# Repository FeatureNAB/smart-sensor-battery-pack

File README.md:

# Smart Sensor Battery Pack
This is the experimental battery charging PCB designed for my YouTube video. You can see the full build process, design theory, and assembly in the video below:

### Please note: 
The design files in this repository include 10k pull-up resistors on the I2C lines (R9 on SCL, R10 on SDA), tied to the switched `3V_SW` rail, so boards built from the current files need no software workaround.

If you have an earlier board that was built without these resistors, software correction is possible using the XIAO pull-ups, and closing the FET early in the boot cycle:

```
# Force GPIO18 LOW (Turns P-Channel MOSFET on)
# Set priority such that this runs before i2c initialises
esphome:
  on_boot:
    - priority: 1200
      then:
        - lambda: |-
            gpio_config_t io_conf = {};
            io_conf.pin_bit_mask = (1ULL<<18);
            io_conf.mode = GPIO_MODE_OUTPUT;
            io_conf.pull_up_en = GPIO_PULLUP_DISABLE;
            io_conf.pull_down_en = GPIO_PULLDOWN_DISABLE;
            io_conf.intr_type = GPIO_INTR_DISABLE;
            gpio_config(&io_conf);
            gpio_set_level(GPIO_NUM_18, 0);

# Software accessible pullups
i2c:
  sda_pullup_enabled: true
  scl_pullup_enabled: true

```

## ⚠️ Safety Warning
This board involves **Lithium-Ion battery charging**. 
*   This is an **experimental prototype** from a hobbyist. **I am not a professional engineer**. It has **not** been certified by safety agencies (UL, CE, etc.).
*   Lithium batteries can be dangerous if mishandled (risk of thermal runaway, fire, explosion, and serious injury).
*   **DO NOT leave this device unattended with a battery connected**
*   By using these files, you agree that you are solely responsible for verifying the safety of the circuit.

## License & Liability

### 1. Non-Commercial Use Only
This project is shared under the [Creative Commons Attribution-NonCommercial-ShareAlike 4.0 International](https://creativecommons.org/licenses/by-nc-sa/4.0/) license.
*  **You are free to:** Download, modify, and build this for personal use or learning.
*  **You may NOT:** Sell this board, use it in a product you sell, or use these files for any commercial purpose.
*  If you modify and share this design, you must share it under this same license.

### 2. No Liability (Disclaimer)
These files are provided "As Is" for educational purposes ONLY. I am sharing my personal project notes. **I accept no liability for any damage, injury, or loss** that occurs from the use or assembly of these files. Use them at your own risk.

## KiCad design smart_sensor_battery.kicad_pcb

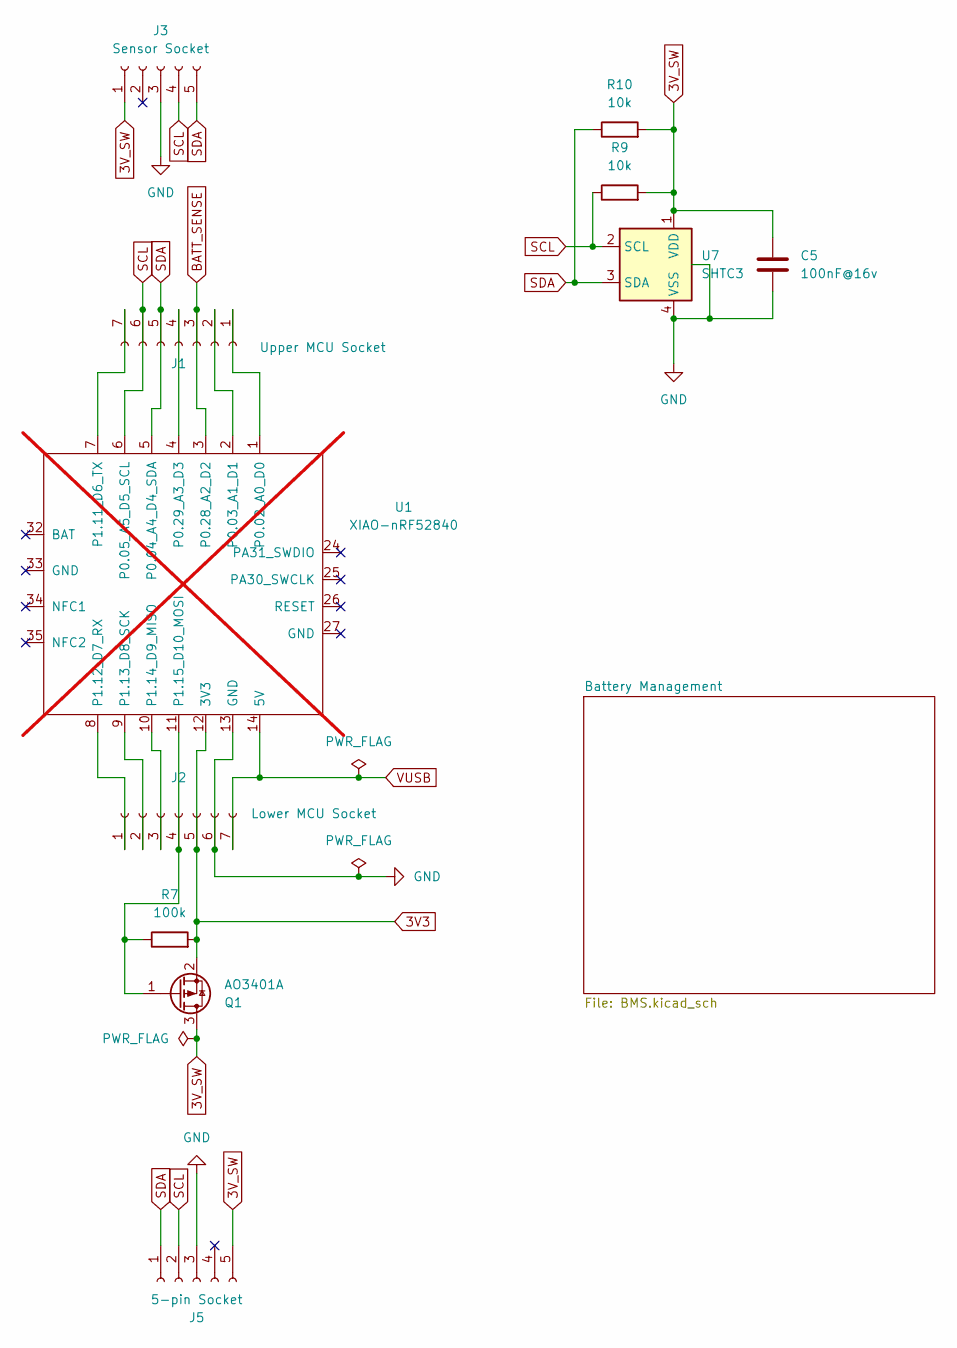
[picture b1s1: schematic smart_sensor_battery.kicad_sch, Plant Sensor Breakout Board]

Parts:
C5: 100nF@16v; C_0402_1005Metric; LCSC Part no. C1525
J1: Upper MCU Socket; PinSocket_1x07_P2.54mm_Vertical_SMD_Pin1Left; LCSC Part no. C42379199
J2: Lower MCU Socket; PinSocket_1x07_P2.54mm_Vertical_SMD_Pin1Right; LCSC Part no. C42379199
J3: Sensor Socket; PinSocket_1x07_P2.54mm_Vertical_SMD_Pin1Right; LCSC Part no. C42379199
J5: 5-pin Socket; PinSocket_1x05_P2.54mm_Vertical_SMD_Pin1Left; LCSC Part no. C42379198
Q1: AO3401A; SOT-23; LCSC Part no. C15127
R7: 100k; R_0402_1005Metric; LCSC Part no. C25530
R9, R10: 10k; R_0402_1005Metric; LCSC Part no. C25744
U1: XIAO-nRF52840; XIAO-nRF52840-SMD; not fitted
U7: SHTC3; Sensirion_DFN-4-1EP_2x2mm_P1mm_EP0.7x1.6mm

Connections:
3V3: J2.5, Q1.2 (S), R7.2, U1.12 (3V3); also elsewhere on the board
3V_SW: C5.1, J3.1, J5.5, Q1.3 (D), R9.2, R10.2, U7.1 (VDD)
BATT_SENSE: J1.3, U1.3 (P0.28_A2_D2); also elsewhere on the board
GND: C5.2, J2.6, J3.3, J5.3, U1.13 (GND), U7.4 (VSS), U7.5 (GND_(centre_pad)); also elsewhere on the board
unnamed: J1.1, U1.1 (P0.02_A0_D0)
unnamed: J1.2, U1.2 (P0.03_A1_D1)
unnamed: J1.4, U1.4 (P0.29_A3_D3)
unnamed: J1.7, U1.7 (P1.11_D6_TX)
unnamed: J2.1, U1.8 (P1.12_D7_RX)
unnamed: J2.2, U1.9 (P1.13_D8_SCK)
unnamed: J2.3, U1.10 (P1.14_D9_MISO)
unnamed: J2.4, Q1.1 (G), R7.1, U1.11 (P1.15_D10_MOSI)
SCL: J1.6, J3.4, J5.2, R9.1, U1.6 (P0.05_A5_D5_SCL), U7.2 (SCL)
SDA: J1.5, J3.5, J5.1, R10.1, U1.5 (P0.04_A4_D4_SDA), U7.3 (SDA)
VUSB: J2.7, U1.14 (5V); also elsewhere on the board

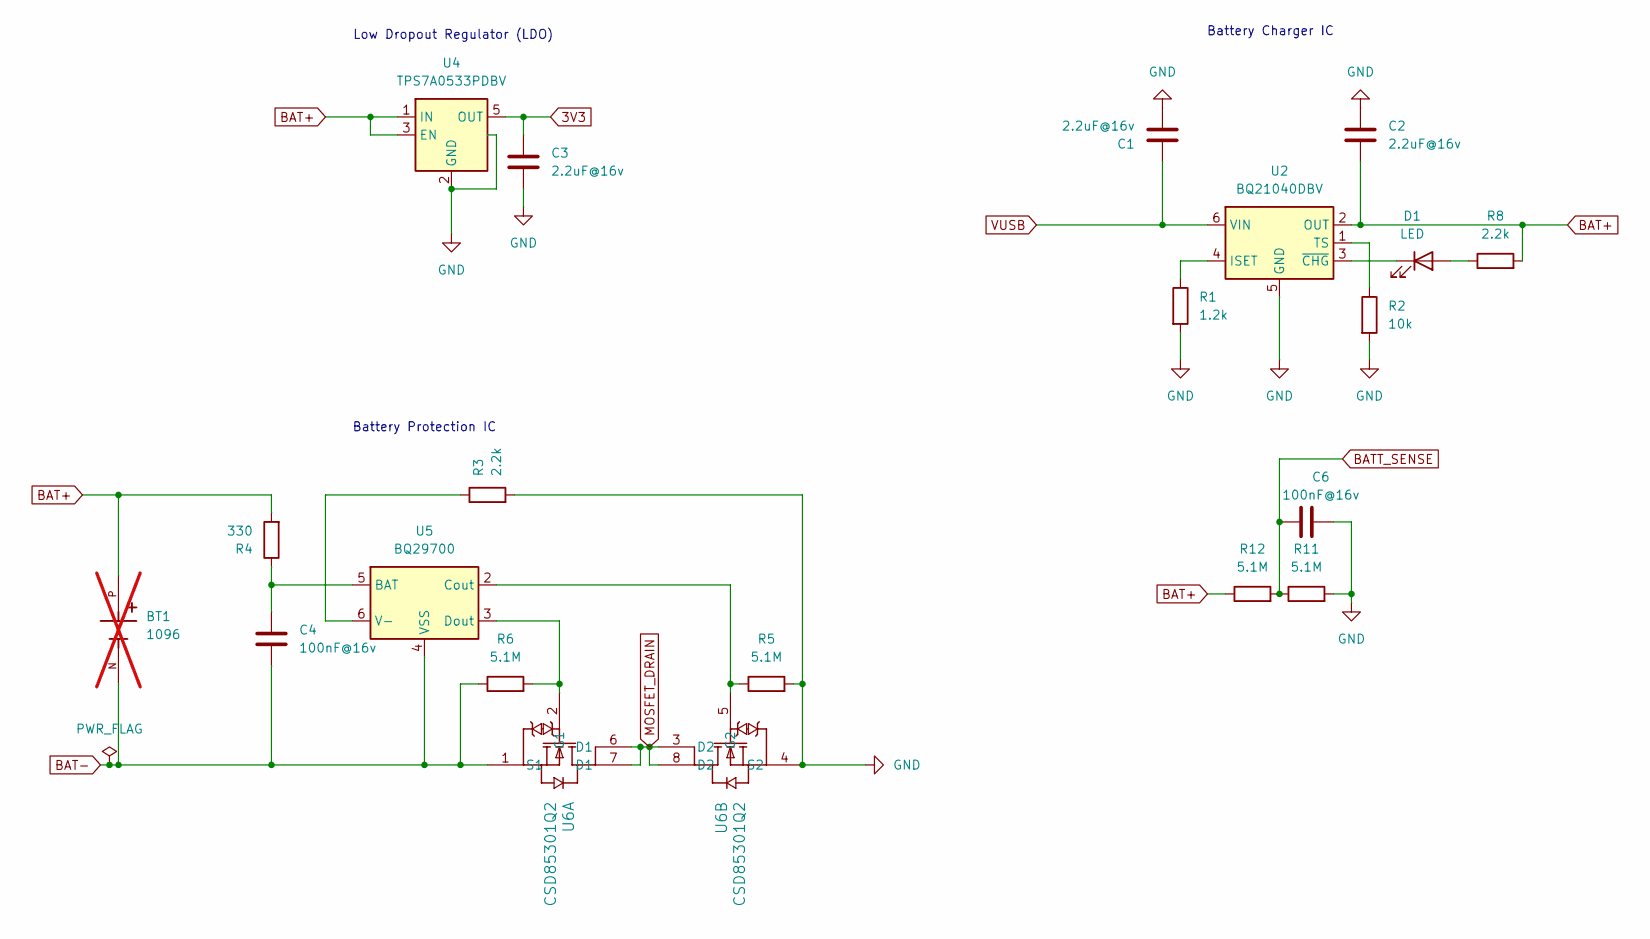
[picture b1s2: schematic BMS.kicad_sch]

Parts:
BT1: 1096; BAT_1096; PARTREV A; not fitted
C1, C2, C3: 2.2uF@16v; C_0603_1608Metric; LCSC Part no. C23630
C4, C6: 100nF@16v; C_0402_1005Metric; LCSC Part no. C1525
D1: LED; LED_0402_1005Metric; LCSC Part no. C74339
R1: 1.2k; R_0402_1005Metric; LCSC Part no. C25862
R2: 10k; R_0402_1005Metric; LCSC Part no. C25744
R3, R8: 2.2k; R_0402_1005Metric; LCSC Part no. C25879
R4: 330; R_0402_1005Metric; LCSC Part no. C25104
R5, R6, R11, R12: 5.1M; R_0402_1005Metric; LCSC Part no. C26092
U2: BQ21040DBV; SOT-23-6; LCSC Part no. C202311
U4: TPS7A0533PDBV; SOT-23-5; LCSC Part no. C493453
U5: BQ29700; WSON-6_1.5x1.5mm_P0.5mm; LCSC Part no. C183096
U6: CSD85301Q2; LCSC Part no. C544396

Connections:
3V3: C3.1, U4.5 (OUT); also elsewhere on the board
BAT+: BT1.P, C2.1, R4.2, R8.2, R12.1, U2.2 (OUT), U4.1 (IN), U4.3 (EN)
BAT-: BT1.N, C4.2, R6.1, U5.4 (VSS), U6.1 (S1)
BATT_SENSE: C6.1, R11.1, R12.2; also elsewhere on the board
GND: C1.2, C2.2, C3.2, C6.2, R1.2, R2.2, R3.2, R5.2, R11.2, U2.5 (GND), U4.2 (GND), U4.4 (NC_(GND)), U6.4 (S2); also elsewhere on the board
MOSFET_DRAIN: U6.3 (D2), U6.6 (D1), U6.7 (D1), U6.8 (D2)
unnamed: D1.2 (A), R8.1
unnamed: D1.1 (K), U2.3 (~CHG)
unnamed: R1.1, U2.4 (ISET)
unnamed: R2.1, U2.1 (TS)
unnamed: C4.1, R4.1, U5.5 (BAT)
unnamed: R5.1, U5.2 (Cout), U6.5 (G2)
unnamed: R6.2, U5.3 (Dout), U6.2 (G1)
unnamed: R3.1, U5.6 (V-)
VUSB: C1.1, U2.6 (VIN); also elsewhere on the board

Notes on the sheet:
Battery Protection IC
Battery Charger IC
Low Dropout Regulator (LDO)

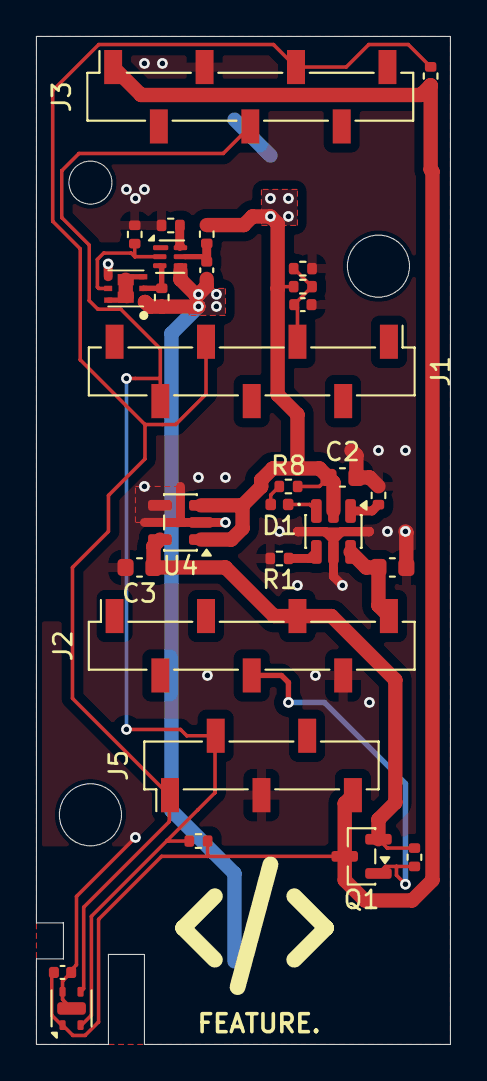
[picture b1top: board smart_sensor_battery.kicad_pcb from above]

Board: 2 copper layers, 23.0 x 56.0 mm, 30 parts (1 on the bottom side), 19 nets.

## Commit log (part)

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2026-02-01 Added README
